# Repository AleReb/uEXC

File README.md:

# uEXC
expansion port for uConsole
based on # https://github.com/PotatoMania/uconsole-expansion-card-template-kicad.git

I'm now generously releasing a simple KiCAD template for customizing uConsole expansion cards. This original work was for a custom expansion card which ceased production.

This is not a standard KiCAD template but rather a project skeleton.

- PCB contains 2 layers, and the thickness is 1 mm.
- The board outline was drawn/traced with FreeCAD.

Do not move the footprints of speakers or mini PCIe connector.

Use at your own risk. The data is not guaranteed to be accurate.
## Créditos y Referencias

Este proyecto se ha desarrollado tomando como referencia y basándose en el excelente trabajo de la comunidad, en particular en los siguientes recursos:

* **uConsole Expansion Card Template KiCad:** [https://github.com/PotatoMania/uconsole-expansion-card-template-kicad](https://github.com/PotatoMania/uconsole-expansion-card-template-kicad)
* **UPico Expansion Card (Foro ClockworkPi):** [https://forum.clockworkpi.com/t/upico-expansion-card/11320](https://forum.clockworkpi.com/t/upico-expansion-card/11320)
* **uEXB - Basic Expansion Board for uConsole (Foro ClockworkPi):** [https://forum.clockworkpi.com/t/uexb-basic-expansion-board-for-uconsole/18071](https://forum.clockworkpi.com/t/uexb-basic-expansion-board-for-uconsole/18071)

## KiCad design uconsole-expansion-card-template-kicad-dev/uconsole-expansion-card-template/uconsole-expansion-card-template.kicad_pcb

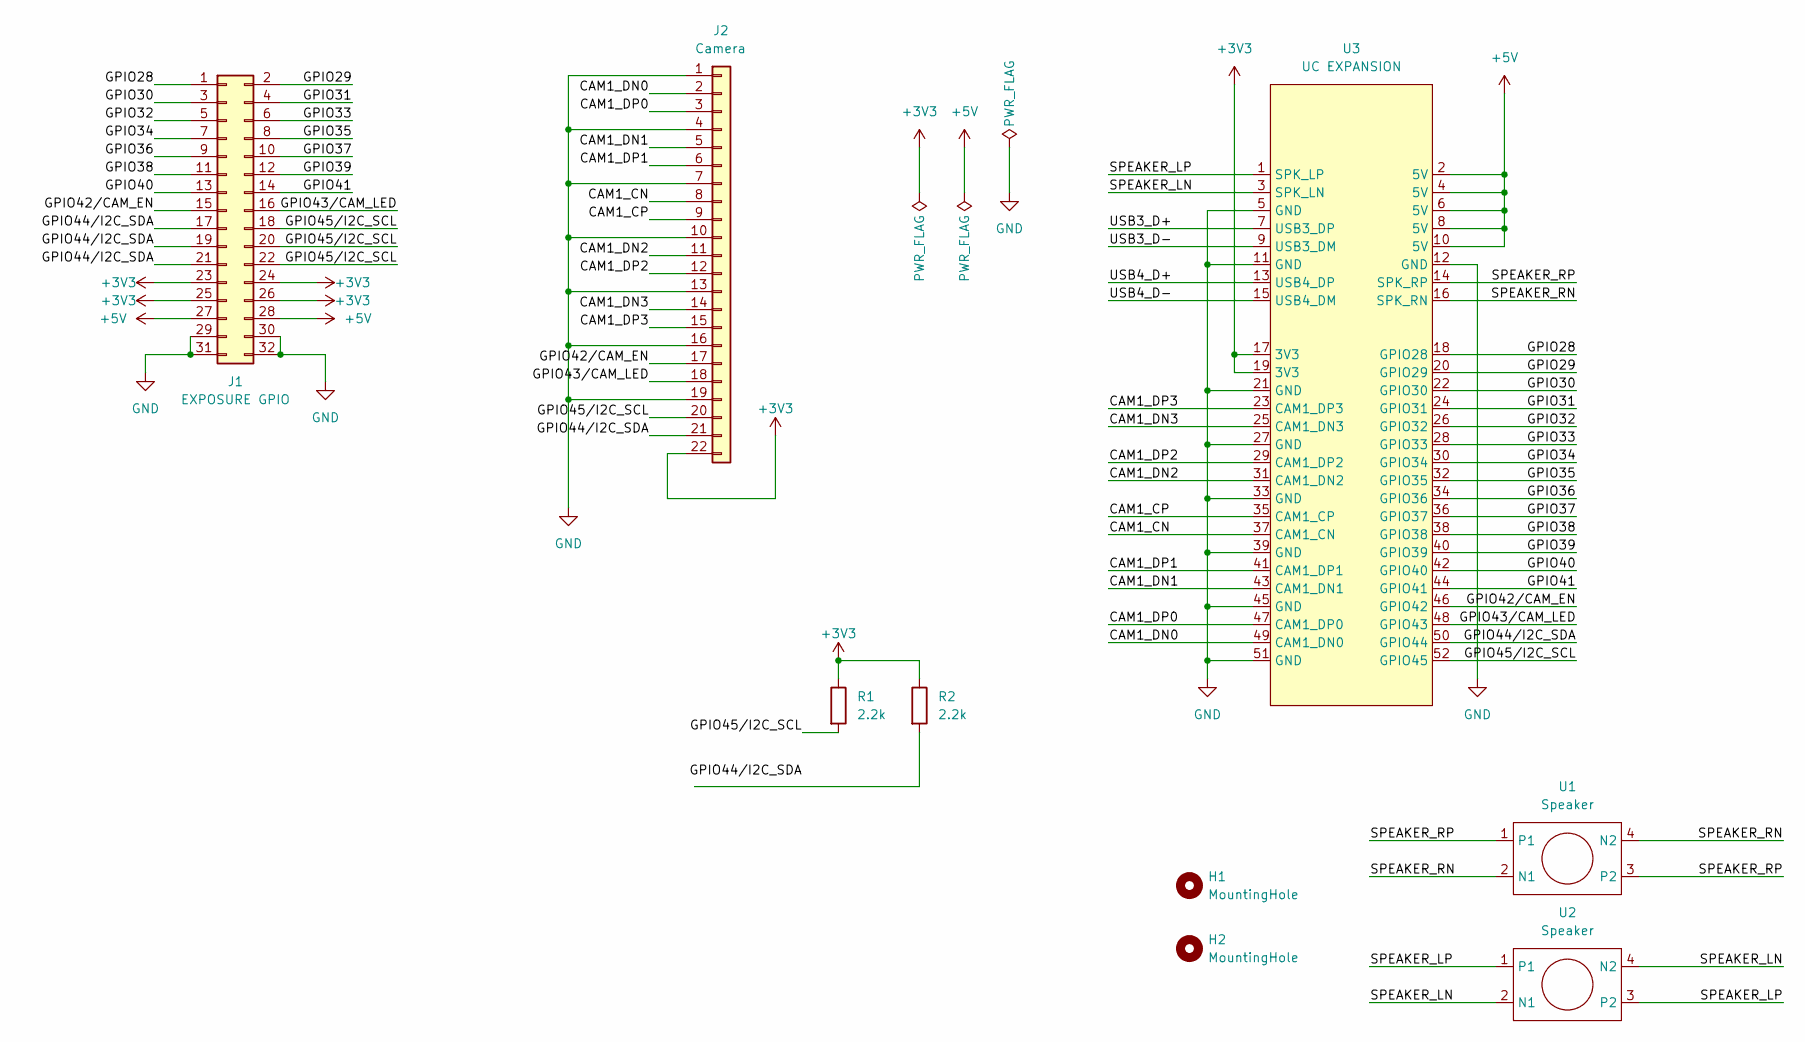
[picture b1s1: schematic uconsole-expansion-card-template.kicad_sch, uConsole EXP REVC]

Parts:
H1, H2: MountingHole; MountingHole_5mm
J1: EXPOSURE GPIO; PinSocket_2x16_P2.54mm_Horizontal
J2: Camera; Hirose_FH12-22S-0.5SH_1x22-1MP_P0.50mm_Horizontal
R1, R2: 2.2k; R_Axial_DIN0204_L3.6mm_D1.6mm_P5.08mm_Horizontal
U1, U2: Speaker; speaker pads
U3: UC EXPANSION; edge-minipcie

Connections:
+3V3: J1.23, J1.24, J1.25, J1.26, J2.22, R1.1, R2.1, U3.17 (3V3), U3.19 (3V3)
+5V: J1.27, J1.28, U3.2 (5V), U3.4 (5V), U3.6 (5V), U3.8 (5V), U3.10 (5V)
/CAM1_CN: J2.8, U3.37 (CAM1_CN)
/CAM1_CP: J2.9, U3.35 (CAM1_CP)
/CAM1_DN0: J2.2, U3.49 (CAM1_DN0)
/CAM1_DN1: J2.5, U3.43 (CAM1_DN1)
/CAM1_DN2: J2.11, U3.31 (CAM1_DN2)
/CAM1_DN3: J2.14, U3.25 (CAM1_DN3)
/CAM1_DP0: J2.3, U3.47 (CAM1_DP0)
/CAM1_DP1: J2.6, U3.41 (CAM1_DP1)
/CAM1_DP2: J2.12, U3.29 (CAM1_DP2)
/CAM1_DP3: J2.15, U3.23 (CAM1_DP3)
/GPIO28: J1.1, U3.18 (GPIO28)
/GPIO29: J1.2, U3.20 (GPIO29)
/GPIO30: J1.3, U3.22 (GPIO30)
/GPIO31: J1.4, U3.24 (GPIO31)
/GPIO32: J1.5, U3.26 (GPIO32)
/GPIO33: J1.6, U3.28 (GPIO33)
/GPIO34: J1.7, U3.30 (GPIO34)
/GPIO35: J1.8, U3.32 (GPIO35)
/GPIO36: J1.9, U3.34 (GPIO36)
/GPIO37: J1.10, U3.36 (GPIO37)
/GPIO38: J1.11, U3.38 (GPIO38)
/GPIO39: J1.12, U3.40 (GPIO39)
/GPIO40: J1.13, U3.42 (GPIO40)
/GPIO41: J1.14, U3.44 (GPIO41)
/GPIO42/CAM_EN: J1.15, J2.17, U3.46 (GPIO42)
/GPIO43/CAM_LED: J1.16, J2.18, U3.48 (GPIO43)
/GPIO44/I2C_SDA: J1.17, J1.19, J1.21, J2.21, U3.50 (GPIO44)
/GPIO45/I2C_SCL: J1.18, J1.20, J1.22, J2.20, R1.2, U3.52 (GPIO45)
/SPEAKER_LN: U2.2 (N1), U2.4 (N2), U3.3 (SPK_LN)
/SPEAKER_LP: U2.1, U2.3 (P2), U3.1 (SPK_LP)
/SPEAKER_RN: U1.2 (N1), U1.4 (N2), U3.16 (SPK_RN)
/SPEAKER_RP: U1.1, U1.3 (P2), U3.14 (SPK_RP)
/USB3_D+: U3.7 (USB3_DP)
/USB3_D-: U3.9 (USB3_DM)
/USB4_D+: U3.13 (USB4_DP)
/USB4_D-: U3.15 (USB4_DM)
GND: J1.29, J1.30, J1.31, J1.32, J2.1, J2.4, J2.7, J2.10, J2.13, J2.16, J2.19, U3.5 (GND), U3.11 (GND), U3.12 (GND), U3.21 (GND), U3.27 (GND), U3.33 (GND), U3.39 (GND), U3.45 (GND), U3.51 (GND)

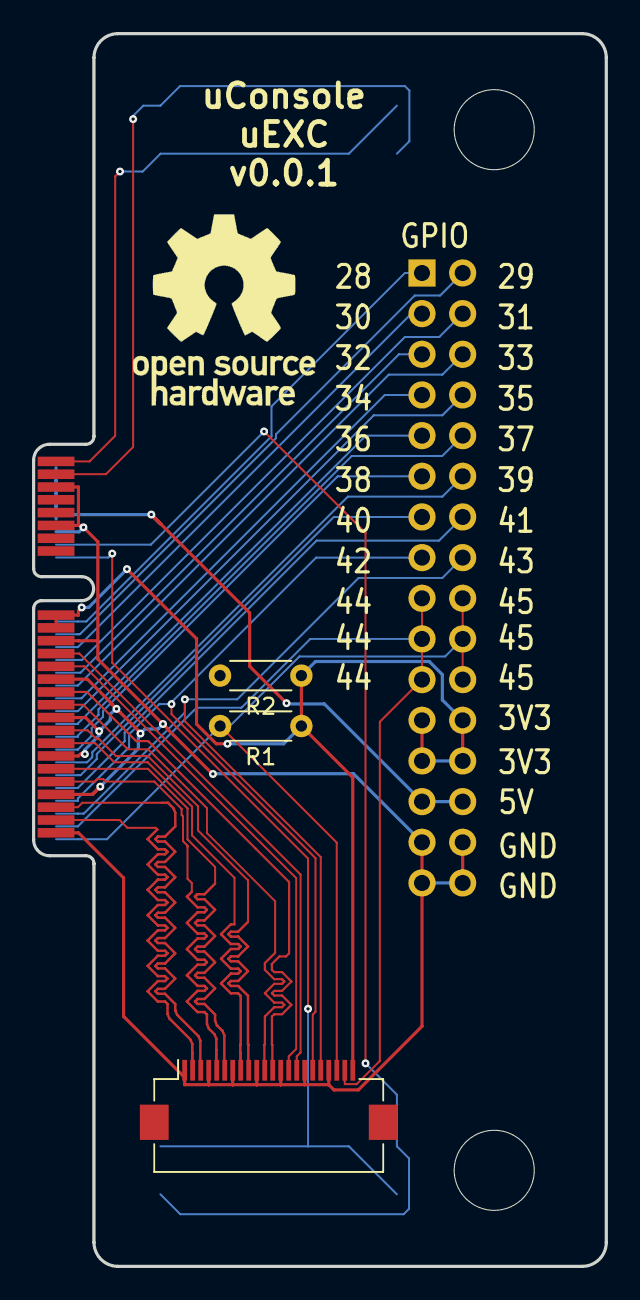
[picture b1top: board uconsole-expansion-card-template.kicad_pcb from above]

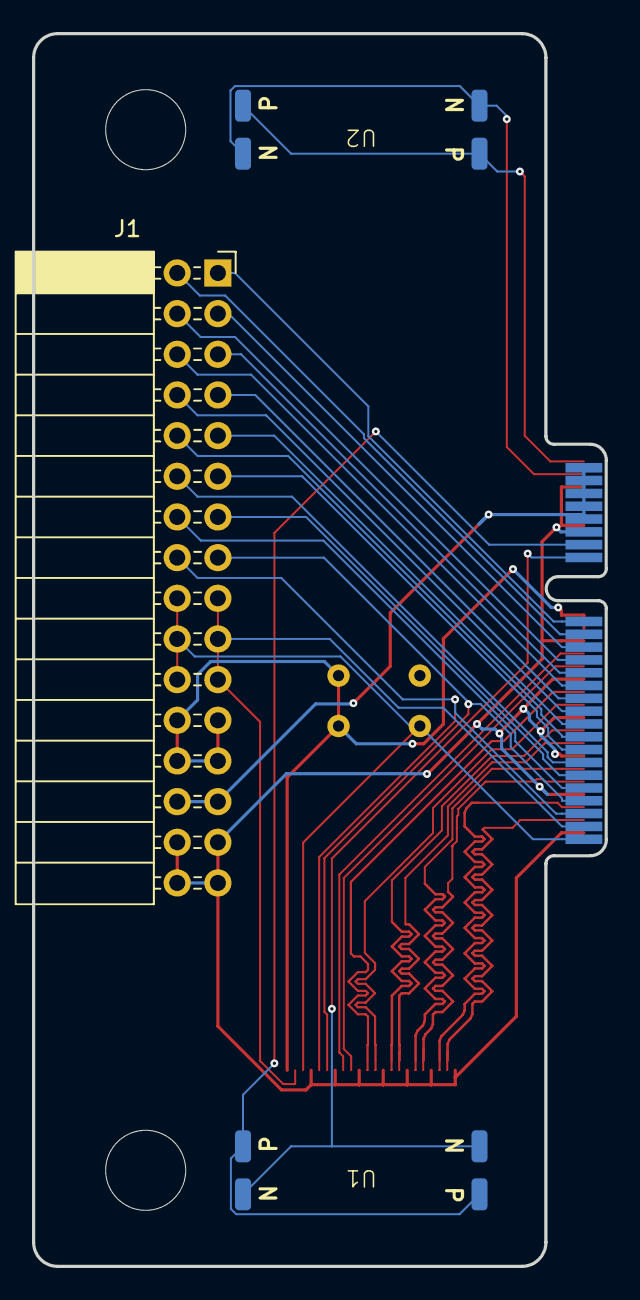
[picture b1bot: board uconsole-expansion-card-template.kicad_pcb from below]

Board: 2 copper layers, 35.8 x 77.0 mm, 9 parts (3 on the bottom side), 35 nets.

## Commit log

2025-06-23 Update LICENSE
